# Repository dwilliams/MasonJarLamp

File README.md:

# MasonJarLamp
Making a board to turn a mason jar into an LED lamp

This lamp runs on 12V AC or DC.  The design is intended to be compatible with the 12V AC Garden Lighting systems available at hardware stores.

<a href="https://oshpark.com/shared_projects/kJSMDAXz"></img></a>

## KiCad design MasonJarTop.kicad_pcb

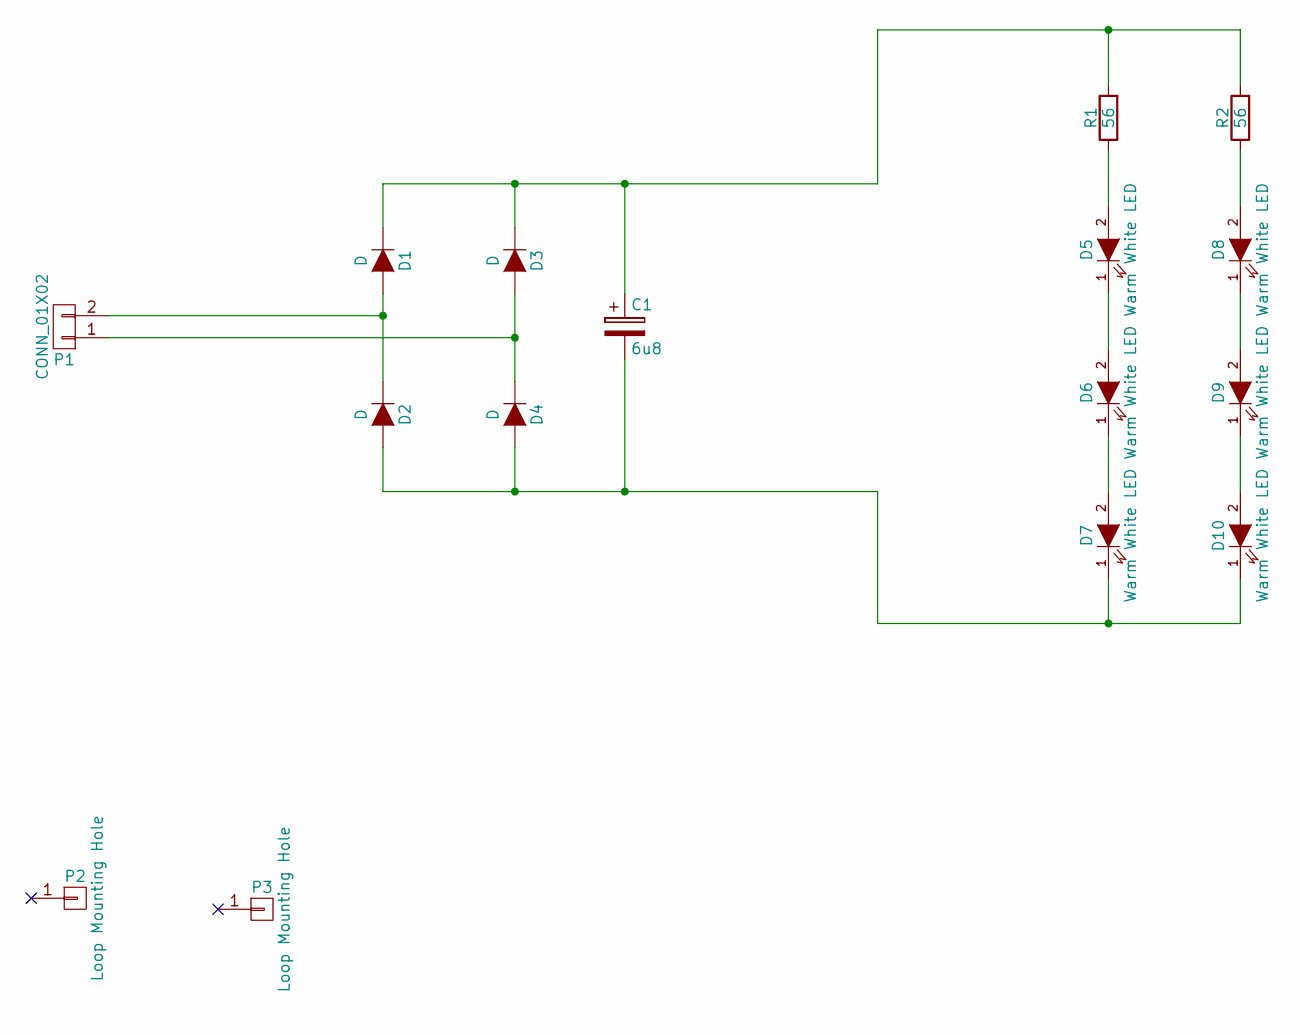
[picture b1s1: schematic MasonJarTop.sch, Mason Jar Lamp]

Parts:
C1: 6u8; c_elec_4x5.3; DigiKey 732-8429-1-ND
D1, D2, D3, D4: D; LED_1206; DigiKey DA2JF2300LCT-ND
D5, D6, D7, D8, D9, D10: Warm White LED; LED_1206; DigiKey 1416-1216-1-ND
P1: CONN_01X02; Pin_Header_Straight_1x02
P2, P3: Loop Mounting Hole; SolderWirePad_single_2mmDrill
R1, R2: 56; R_1206_HandSoldering; DigiKey 311-56ERCT-ND

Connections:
unnamed: C1.1, D1.1 (K), D3.1 (K), R1.2, R2.2
unnamed: C1.2, D2.2 (A), D4.2 (A), D7.1 (K), D10.1 (K)
unnamed: D1.2 (A), D2.1 (K), P1.2
unnamed: D3.2 (A), D4.1 (K), P1.1
unnamed: D5.1 (K), D6.2 (A)
unnamed: D5.2 (A), R1.1
unnamed: D6.1 (K), D7.2 (A)
unnamed: D8.1 (K), D9.2 (A)
unnamed: D8.2 (A), R2.1
unnamed: D9.1 (K), D10.2 (A)

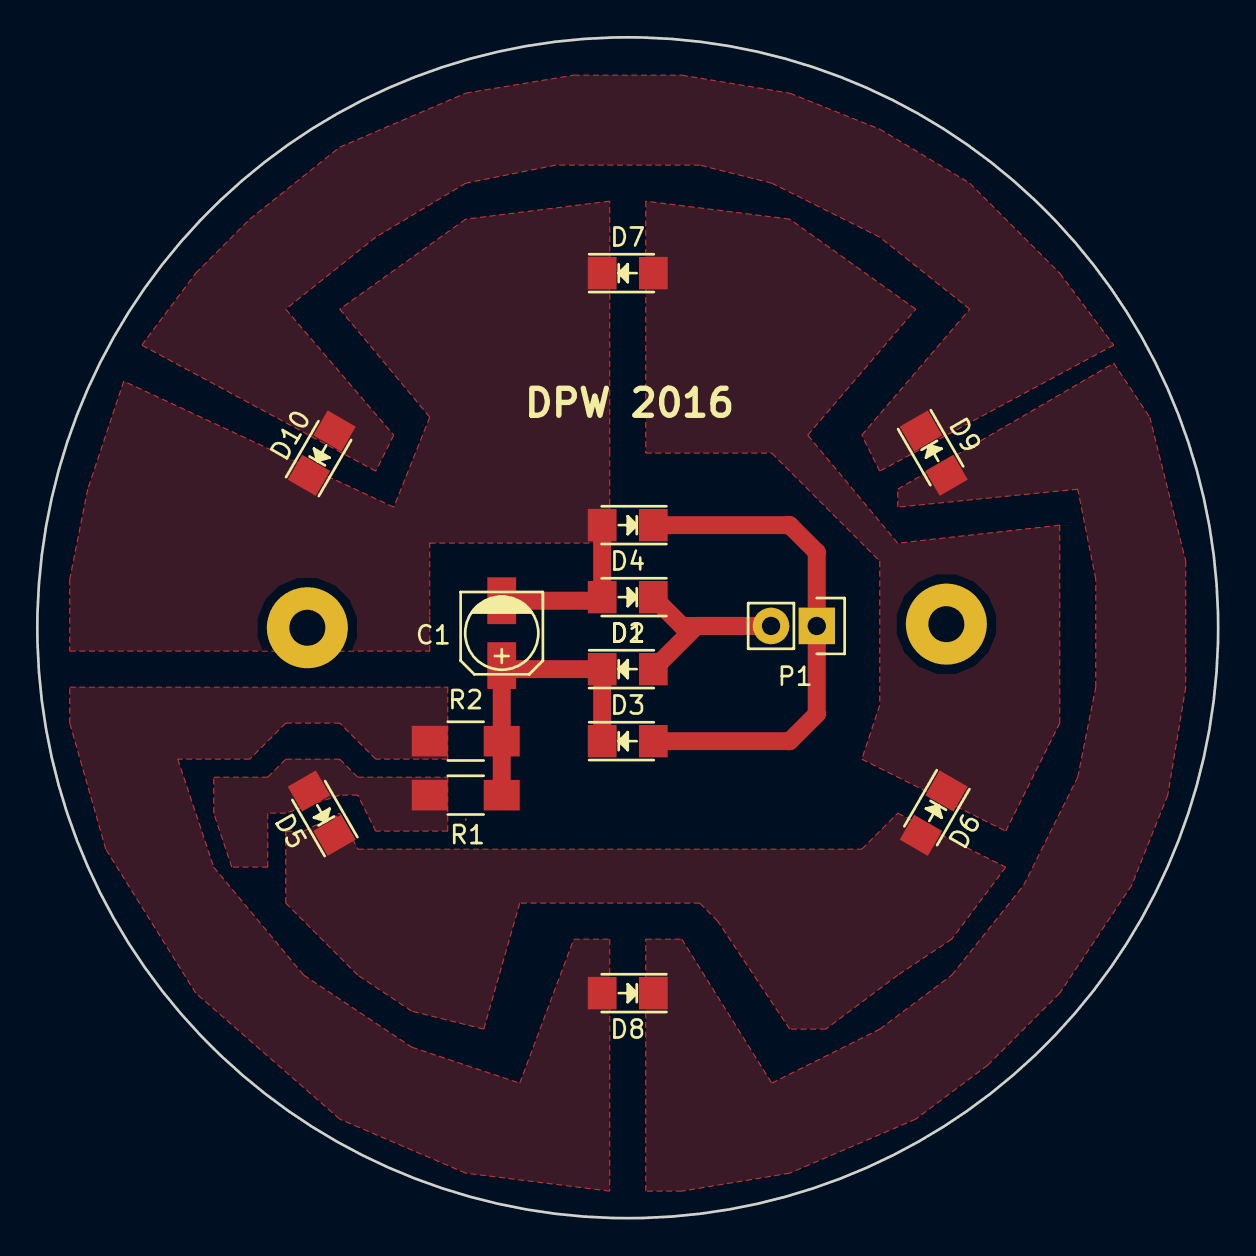
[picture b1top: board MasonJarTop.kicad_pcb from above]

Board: 2 copper layers, 65.6 x 65.6 mm, 16 parts (0 on the bottom side), 10 nets.

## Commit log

2016-06-24 Adding project bits to the repo.
2016-06-24 Moving datasheets to folder.
2016-06-26 Updating schematic to use discrete diodes.
2016-06-26 Renaming datasheet.
2016-06-27 Layout done.
2016-06-27 Finished layout.
2016-06-27 Making the copper pours solid for thermal relief from the LEDs.
2016-06-27 Added BOM generation plugin (I hope).
2016-07-07 Modify schematic after testing and re-layout complete.
